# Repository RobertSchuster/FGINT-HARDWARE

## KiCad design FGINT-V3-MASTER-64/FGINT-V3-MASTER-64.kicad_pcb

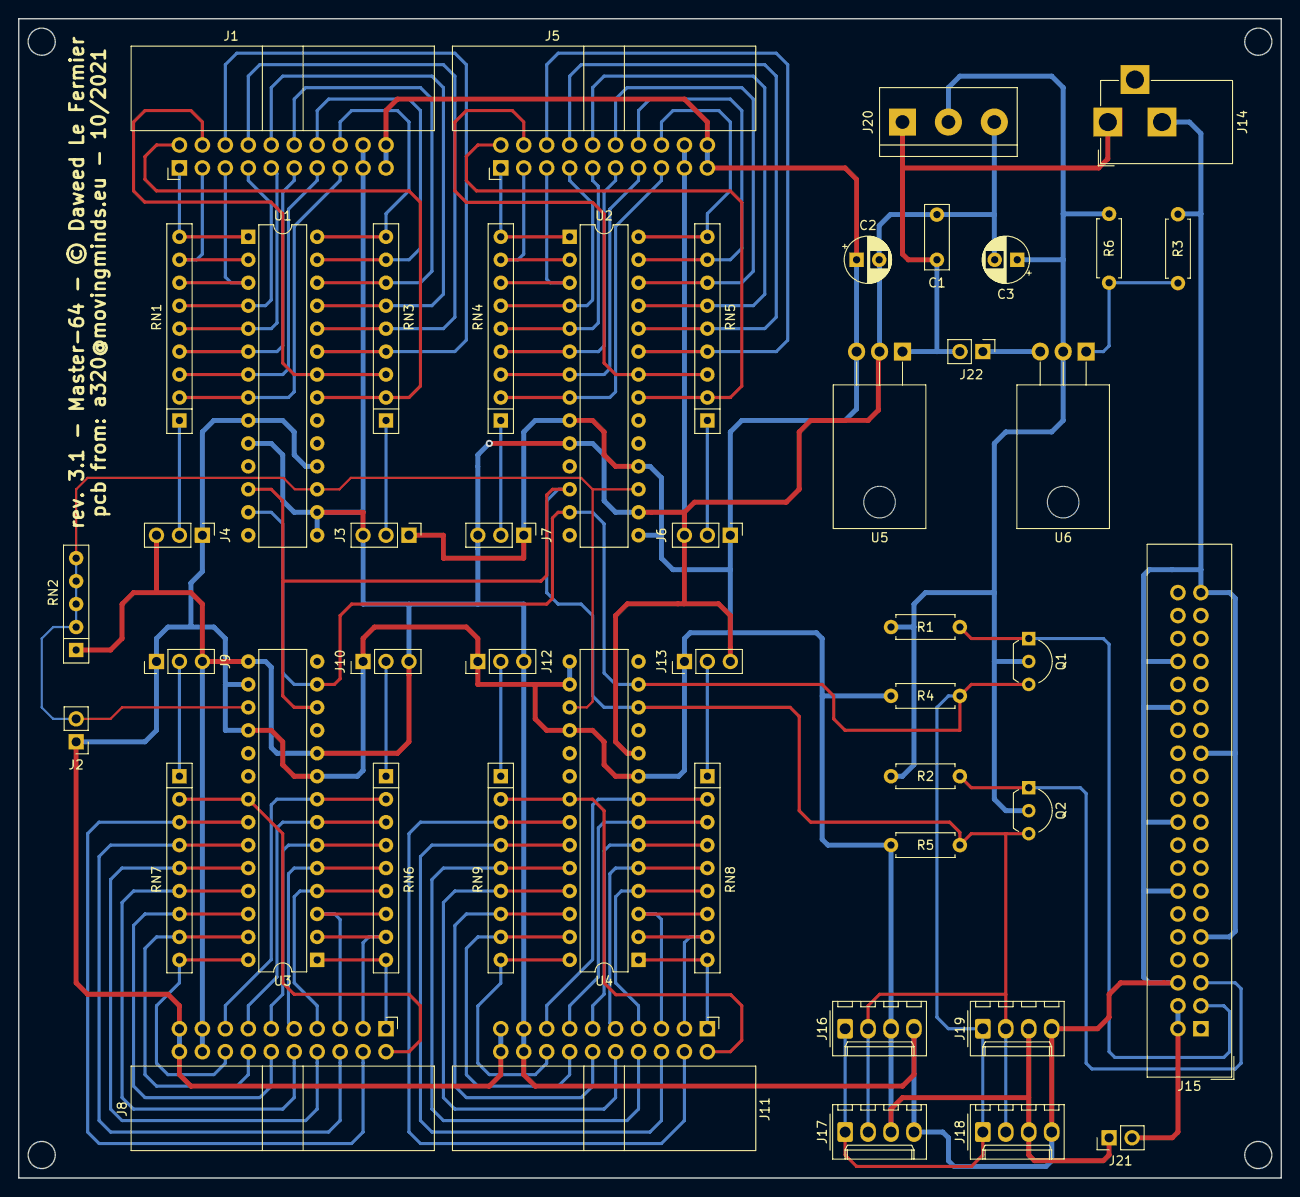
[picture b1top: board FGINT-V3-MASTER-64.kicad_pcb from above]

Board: 2 copper layers, 139.7 x 128.3 mm, 48 parts (0 on the bottom side), 84 nets.

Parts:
C1: 100nF; C_Rect_L7.0mm_W2.5mm_P5.00mm
C2, C3: 1uF; CP_Radial_D5.0mm_P2.50mm
J1: OUT1-16; IDC-Header_2x10_P2.54mm_Horizontal
J2: BOARD SEL ADDR; PinHeader_1x02_P2.54mm_Vertical
J3: ComGPIOA0; PinHeader_1x03_P2.54mm_Vertical
J4: ComGPIOB0; PinHeader_1x03_P2.54mm_Vertical
J5: OUT17-32; IDC-Header_2x10_P2.54mm_Horizontal
J6: ComGPIOA1; PinHeader_1x03_P2.54mm_Vertical
J7: ComGPIOB1; PinHeader_1x03_P2.54mm_Vertical
J8: OUT33-48; IDC-Header_2x10_P2.54mm_Horizontal
J9: ComGPIOA2; PinHeader_1x03_P2.54mm_Vertical
J10: ComGPIOB2; PinHeader_1x03_P2.54mm_Vertical
J11: OUT48-64; IDC-Header_2x10_P2.54mm_Horizontal
J12: ComGPIOA3; PinHeader_1x03_P2.54mm_Vertical
J13: ComGPIOB3; PinHeader_1x03_P2.54mm_Vertical
J14: 9V - 12 DC; BarrelJack_CUI_PJ-102AH_Horizontal
J15: Raspberry; IDC-Header_2x20_P2.54mm_Vertical
J16: Exp 01; Molex_KK-254_AE-6410-04A_1x04_P2.54mm_Vertical
J17: Exp 02; Molex_KK-254_AE-6410-04A_1x04_P2.54mm_Vertical
J18: Exp 03; Molex_KK-254_AE-6410-04A_1x04_P2.54mm_Vertical
J19: Exp 04; Molex_KK-254_AE-6410-04A_1x04_P2.54mm_Vertical
J20: PC Power Input; TerminalBlock_bornier-3_P5.08mm
J21: 5VPI; PinHeader_1x02_P2.54mm_Vertical
J22: 3.3 ENBL; PinHeader_1x02_P2.54mm_Vertical
Q1, Q2: 2N7000; TO-92L_Inline_Wide
R1, R2, R4, R5: 10K; R_Axial_DIN0207_L6.3mm_D2.5mm_P7.62mm_Horizontal
R3: 540; R_Axial_DIN0207_L6.3mm_D2.5mm_P7.62mm_Horizontal
R6: 330; R_Axial_DIN0207_L6.3mm_D2.5mm_P7.62mm_Horizontal
RN1, RN3, RN4, RN5, RN6, RN7, RN8, RN9: 10K Network Res; R_Array_SIP9
RN2: 10K Network Res; R_Array_SIP5
U1, U2, U3, U4: MCP23017_SP; DIP-28_W7.62mm
U5: LM7805; TO-220-3_Horizontal_TabDown
U6: LM317; TO-220-3_Horizontal_TabDown

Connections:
+3V3: C3.1, J20.2, Q1.2, Q2.2, R1.1, R2.1, R6.1, U6.2
+5V: C2.1, J1.19, J1.20, J2.1, J3.1, J4.1, J5.19, J5.20, J6.1, J7.1, J8.19, J8.20, J9.1, J10.1, J11.19, J11.20, J12.1, J13.1, J16.3, J17.3, J18.3, J19.3, J21.1, R4.1, R5.1, U1.9, U1.18, U2.9, U2.15, U2.18, U3.9, U3.16, U3.18, U4.9, U4.15, U4.16, U4.18, U5.3
+12V: C1.1, J14.1, J20.1, J22.2, U5.1
/+5VPI: J15.2, J15.4, J21.2
/A00: J2.2, RN2.2, RN2.3, RN2.4, RN2.5, U1.17, U2.17, U3.17, U4.17
/CA0: J3.2, RN3.1
/CA1: J6.2, RN5.1
/CA2: J9.2, RN7.1
/CA3: J12.2, RN9.1
/CB0: J4.2, RN1.1
/CB1: J7.2, RN4.1
/CB2: J10.2, RN6.1
/CB3: J13.2, RN8.1
/ENBL3.3: J22.1, U6.3
/GPIOA00: J1.2, RN3.2, U1.21
/GPIOA01: J1.4, RN3.3, U1.22
/GPIOA02: J1.6, RN3.4, U1.23
/GPIOA03: J1.8, RN3.5, U1.24
/GPIOA04: J1.10, RN3.6, U1.25
/GPIOA05: J1.12, RN3.7, U1.26
/GPIOA06: J1.14, RN3.8, U1.27
/GPIOA07: J1.16, RN3.9, U1.28
/GPIOA10: J5.2, RN5.2, U2.21
/GPIOA11: J5.4, RN5.3, U2.22
/GPIOA12: J5.6, RN5.4, U2.23
/GPIOA13: J5.8, RN5.5, U2.24
/GPIOA14: J5.10, RN5.6, U2.25
/GPIOA15: J5.12, RN5.7, U2.26
/GPIOA16: J5.14, RN5.8, U2.27
/GPIOA17: J5.16, RN5.9, U2.28
/GPIOA20: J8.2, RN7.2, U3.21
/GPIOA21: J8.4, RN7.3, U3.22
/GPIOA22: J8.6, RN7.4, U3.23
/GPIOA23: J8.8, RN7.5, U3.24
/GPIOA24: J8.10, RN7.6, U3.25
/GPIOA25: J8.12, RN7.7, U3.26
/GPIOA26: J8.14, RN7.8, U3.27
/GPIOA27: J8.16, RN7.9, U3.28
/GPIOA30: J11.2, RN9.2, U4.21
/GPIOA31: J11.4, RN9.3, U4.22
/GPIOA32: J11.6, RN9.4, U4.23
/GPIOA33: J11.8, RN9.5, U4.24
/GPIOA34: J11.10, RN9.6, U4.25
/GPIOA35: J11.12, RN9.7, U4.26
/GPIOA36: J11.14, RN9.8, U4.27
/GPIOA37: J11.16, RN9.9, U4.28
/GPIOB00: J1.1, RN1.9, U1.1
/GPIOB01: J1.3, RN1.8, U1.2
/GPIOB02: J1.5, RN1.7, U1.3
/GPIOB03: J1.7, RN1.6, U1.4
/GPIOB04: J1.9, RN1.5, U1.5
/GPIOB05: J1.11, RN1.4, U1.6
/GPIOB06: J1.13, RN1.3, U1.7
/GPIOB07: J1.15, RN1.2, U1.8
/GPIOB10: J5.1, RN4.9, U2.1
/GPIOB11: J5.3, RN4.8, U2.2
/GPIOB12: J5.5, RN4.7, U2.3
/GPIOB13: J5.7, RN4.6, U2.4
/GPIOB14: J5.9, RN4.5, U2.5
/GPIOB15: J5.11, RN4.4, U2.6
/GPIOB16: J5.13, RN4.3, U2.7
/GPIOB17: J5.15, RN4.2, U2.8
/GPIOB20: J8.1, RN6.9, U3.1
/GPIOB21: J8.3, RN6.8, U3.2
/GPIOB22: J8.5, RN6.7, U3.3
/GPIOB23: J8.7, RN6.6, U3.4
/GPIOB24: J8.9, RN6.5, U3.5
/GPIOB25: J8.11, RN6.4, U3.6
/GPIOB26: J8.13, RN6.3, U3.7
/GPIOB27: J8.15, RN6.2, U3.8
/GPIOB30: J11.1, RN8.9, U4.1
/GPIOB31: J11.3, RN8.8, U4.2
/GPIOB32: J11.5, RN8.7, U4.3
/GPIOB33: J11.7, RN8.6, U4.4
/GPIOB34: J11.9, RN8.5, U4.5
/GPIOB35: J11.11, RN8.4, U4.6
/GPIOB36: J11.13, RN8.3, U4.7
/GPIOB37: J11.15, RN8.2, U4.8
/SCL: J15.5, Q2.1, R2.2
/SCL5V: J16.2, J17.2, J18.2, J19.2, Q2.3, R5.2, U1.12, U2.12, U3.12, U4.12
/SDA: J15.3, Q1.1, R1.2
/SDA5V: J16.1, J17.1, J18.1, J19.1, Q1.3, R4.2, U1.13, U2.13, U3.13, U4.13
GND: C1.2, C2.2, C3.2, J1.17, J1.18, J3.3, J4.3, J5.17, J5.18, J6.3, J7.3, J8.17, J8.18, J9.3, J10.3, J11.17, J11.18, J12.3, J13.3, J14.2, J15.6, J15.9, J15.14, J15.20, J15.25, J15.30, J15.34, J15.39, J16.4, J17.4, J18.4, J19.4, J20.3, R3.2, RN2.1, U1.10, U1.15, U1.16, U2.10, U2.16, U3.10, U3.15, U4.10, U5.2
unnamed: R3.1, R6.2, U6.1

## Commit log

2021-10-12 copyright @daweed added, routing modified
2021-10-12 Gerber-export files modified

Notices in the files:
FGINT-V3-MASTER-64/FGINT-V3-MASTER-64.kicad_pcb:
rev. 3.1 - Master-64 - © Daweed Le Fermier
